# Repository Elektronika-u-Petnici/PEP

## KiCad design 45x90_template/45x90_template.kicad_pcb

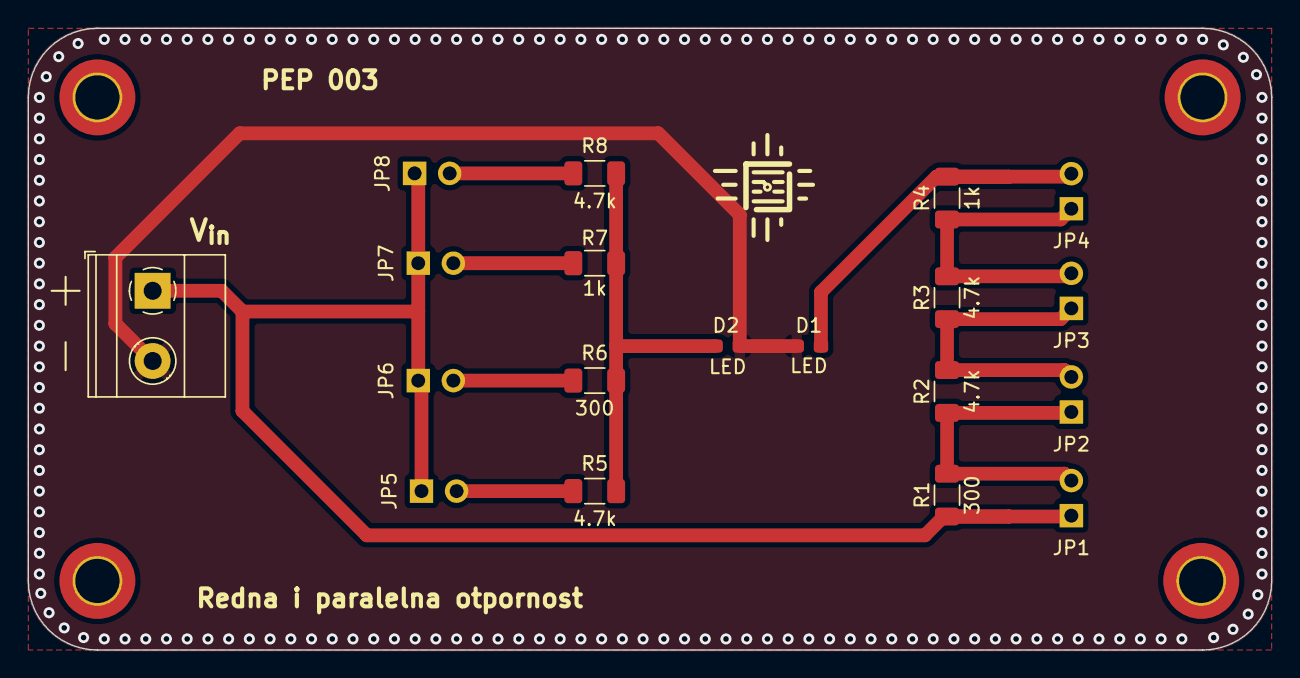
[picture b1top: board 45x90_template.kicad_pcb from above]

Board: 2 copper layers, 90.0 x 45.0 mm, 23 parts (0 on the bottom side), 11 nets.

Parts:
D1, D2: LED; LED_0603_1608Metric_Pad1.05x0.95mm_HandSolder
H1, H2, H3, H4: MountingHole; MountingHole_3.2mm_M3_ISO14580_Pad_TopBottom
J1: Screw_Terminal_01x02; TerminalBlock_Phoenix_MKDS-1,5-2-5.08_1x02_P5.08mm_Horizont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
JP1, JP2, JP3, JP4, JP5, JP6, JP7, JP8: Jumper; PinHeader_1x02_P2.54mm_Vertical
R1, R6: 300; R_smd
R2, R3, R5, R8: 4.7k; R_smd
R4, R7: 1k; R_smd

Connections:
0: D1.1 (K), D2.1 (K), J1.2
9V: J1.1, JP1.1 (A), JP5.1 (A), JP6.1 (A), JP7.1 (A), JP8.1 (A), R1.1
unnamed: D1.2 (A), JP4.2 (B), R4.2
unnamed: D2.2 (A), R5.1, R6.2, R7.2, R8.1
unnamed: JP1.2 (B), JP2.1 (A), R1.2, R2.1
unnamed: JP2.2 (B), JP3.1 (A), R2.2, R3.1
unnamed: JP3.2 (B), JP4.1 (A), R3.2, R4.1
unnamed: JP5.2 (B), R5.2
unnamed: JP6.2 (B), R6.1
unnamed: JP7.2 (B), R7.1
unnamed: JP8.2 (B), R8.2

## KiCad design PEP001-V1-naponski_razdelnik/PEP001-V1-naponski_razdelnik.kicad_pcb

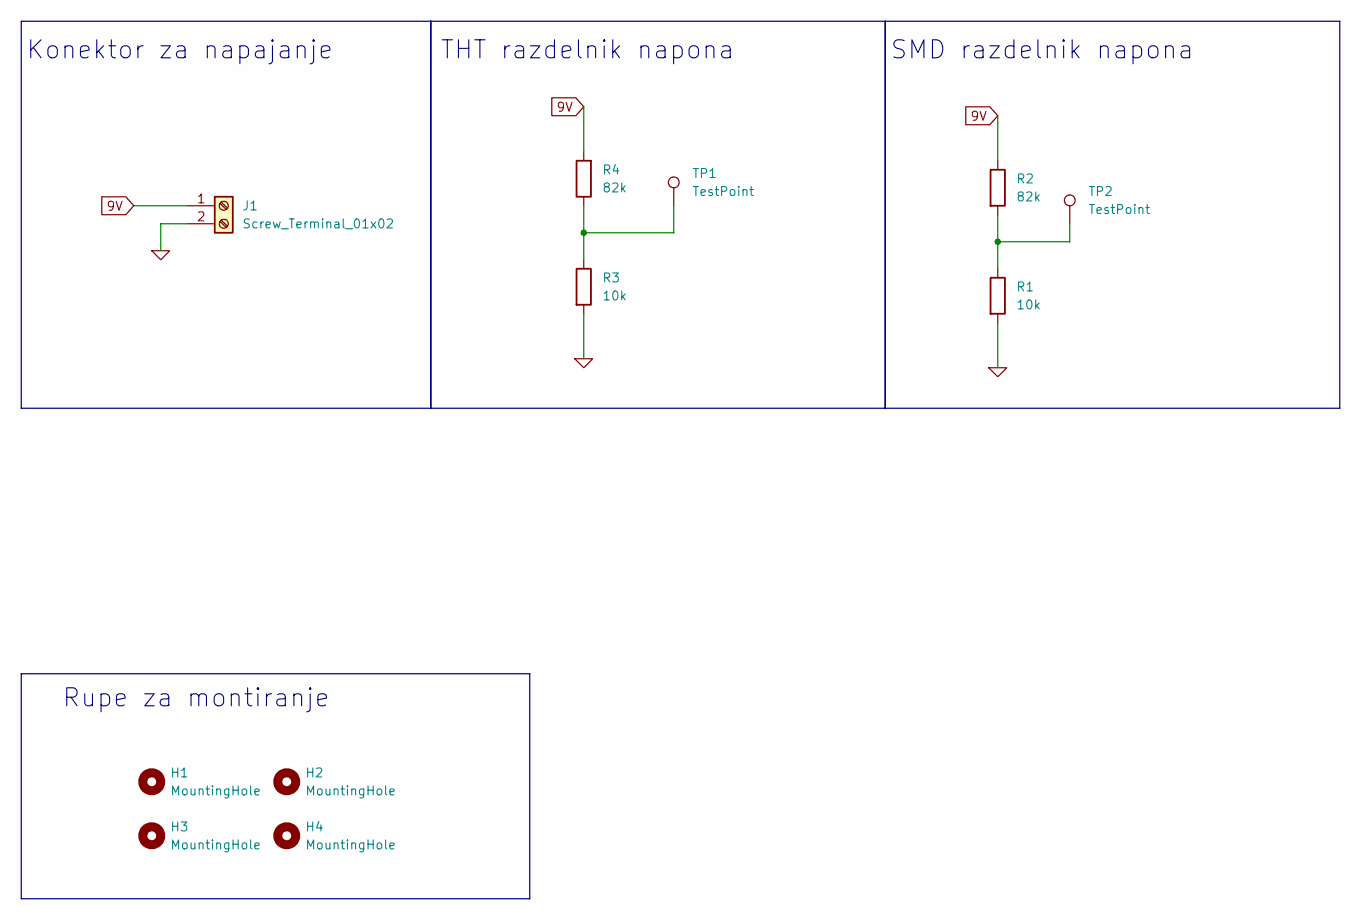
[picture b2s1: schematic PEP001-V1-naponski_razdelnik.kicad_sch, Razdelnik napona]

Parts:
H1, H2, H3, H4: MountingHole; MountingHole_3.2mm_M3_ISO14580_Pad_TopBottom
J1: Screw_Terminal_01x02; TerminalBlock_Phoenix_MKDS-1,5-2-5.08_1x02_P5.08mm_Horizont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; LCSC C3018698
R1: 10k; R_1206_3216Metric_Pad1.30x1.75mm_HandSolder; LCSC C17902
R2: 82k; R_1206_3216Metric_Pad1.30x1.75mm_HandSolder; LCSC C17979
R3: 10k; R_Axial_DIN0207_L6.3mm_D2.5mm_P15.24mm_Horizontal; LCSC C410695
R4: 82k; R_Axial_DIN0207_L6.3mm_D2.5mm_P15.24mm_Horizontal; LCSC C601724
TP1, TP2: TestPoint; TestPoint_Pad_D2.5mm

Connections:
0: J1.2, R1.2, R3.2
9V: J1.1, R2.1, R4.2
unnamed: R1.1, R2.2, TP2.1
unnamed: R3.1, R4.1, TP1.1

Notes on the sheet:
SMD razdelnik napona
Rupe za montiranje
Konektor za napajanje
THT razdelnik napona

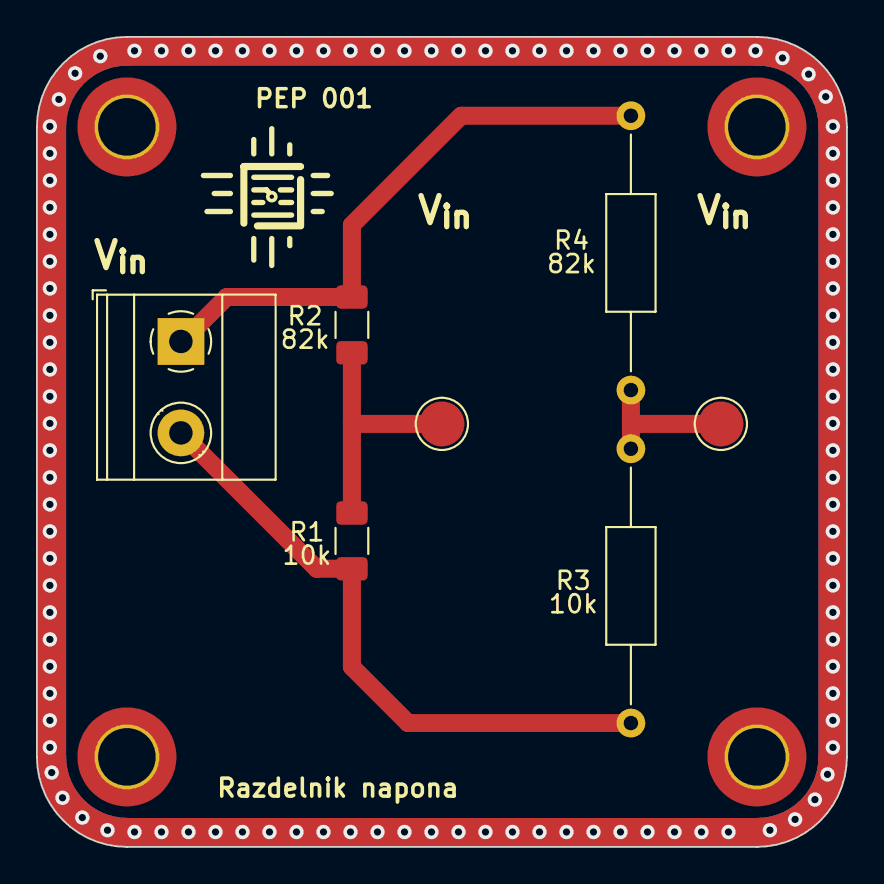
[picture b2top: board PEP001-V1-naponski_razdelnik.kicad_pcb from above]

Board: 2 copper layers, 45.0 x 45.0 mm, 11 parts (0 on the bottom side), 4 nets.

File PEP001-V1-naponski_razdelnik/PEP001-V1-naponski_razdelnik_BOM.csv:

"Comment","Designator","Footprint","LCSC Part Number"
"MountingHole,TestPoint","H1,H2,H3,H4,TP1,TP2","",""
"Screw_Terminal_01x02","J1","THT","C3018698"
"10k","R1","1206","C17902"
"82k","R2","1206","C17979"
"10k","R3","THT","C410695"
"82k","R4","THT","C601724"

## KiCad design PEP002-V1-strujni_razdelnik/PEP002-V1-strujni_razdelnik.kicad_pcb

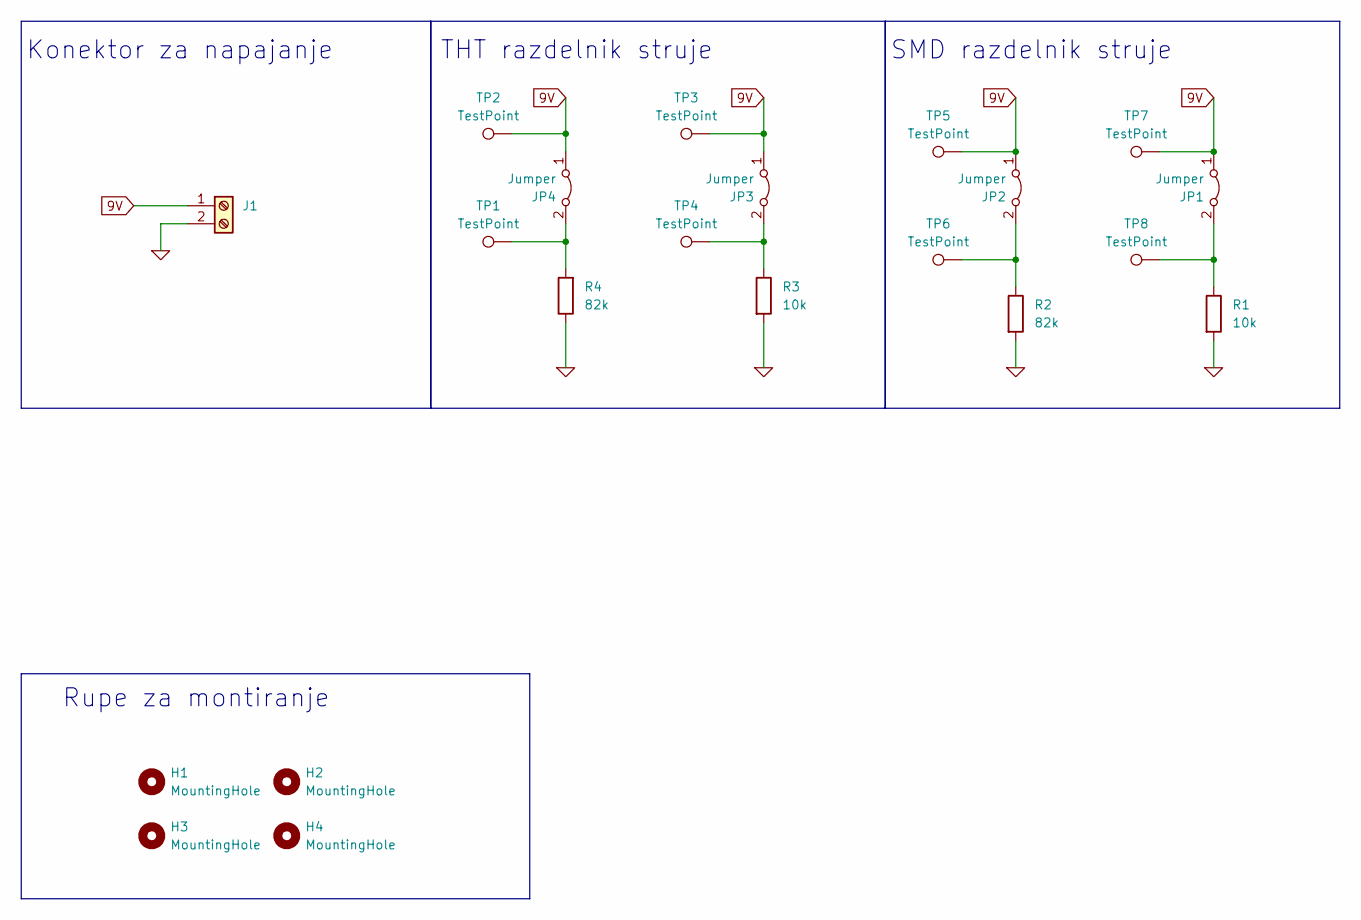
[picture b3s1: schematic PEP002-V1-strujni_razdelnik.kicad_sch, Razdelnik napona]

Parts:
H1, H2, H3, H4: MountingHole; MountingHole_3.2mm_M3_ISO14580_Pad_TopBottom
J1: Screw_Terminal_01x02; TerminalBlock_Phoenix_MKDS-1,5-2-5.08_1x02_P5.08mm_Horizont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; LCSC Part Number C3018698
JP1, JP2, JP3, JP4: Jumper; PinHeader_1x02_P2.54mm_Vertical; LCSC Part Number C492401
R1: 10k; R_1206_3216Metric_Pad1.30x1.75mm_HandSolder; LCSC Part Number C17902
R2: 82k; R_1206_3216Metric_Pad1.30x1.75mm_HandSolder; LCSC Part Number C17979
R3: 10k; R_Axial_DIN0207_L6.3mm_D2.5mm_P15.24mm_Horizontal; LCSC Part Number C410695
R4: 82k; R_Axial_DIN0207_L6.3mm_D2.5mm_P15.24mm_Horizontal; LCSC Part Number C601724
TP1, TP2, TP3, TP4, TP5, TP6, TP7, TP8: TestPoint; TestPoint_Pad_D2.5mm

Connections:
0: J1.2, R1.2, R2.2, R3.2, R4.1
9V: J1.1, JP1.1 (A), JP2.1 (A), JP3.1 (A), JP4.1 (A), TP2.1, TP3.1, TP5.1, TP7.1
unnamed: JP1.2 (B), R1.1, TP8.1
unnamed: JP2.2 (B), R2.1, TP6.1
unnamed: JP3.2 (B), R3.1, TP4.1
unnamed: JP4.2 (B), R4.2, TP1.1

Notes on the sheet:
SMD razdelnik struje
Rupe za montiranje
Konektor za napajanje
THT razdelnik struje

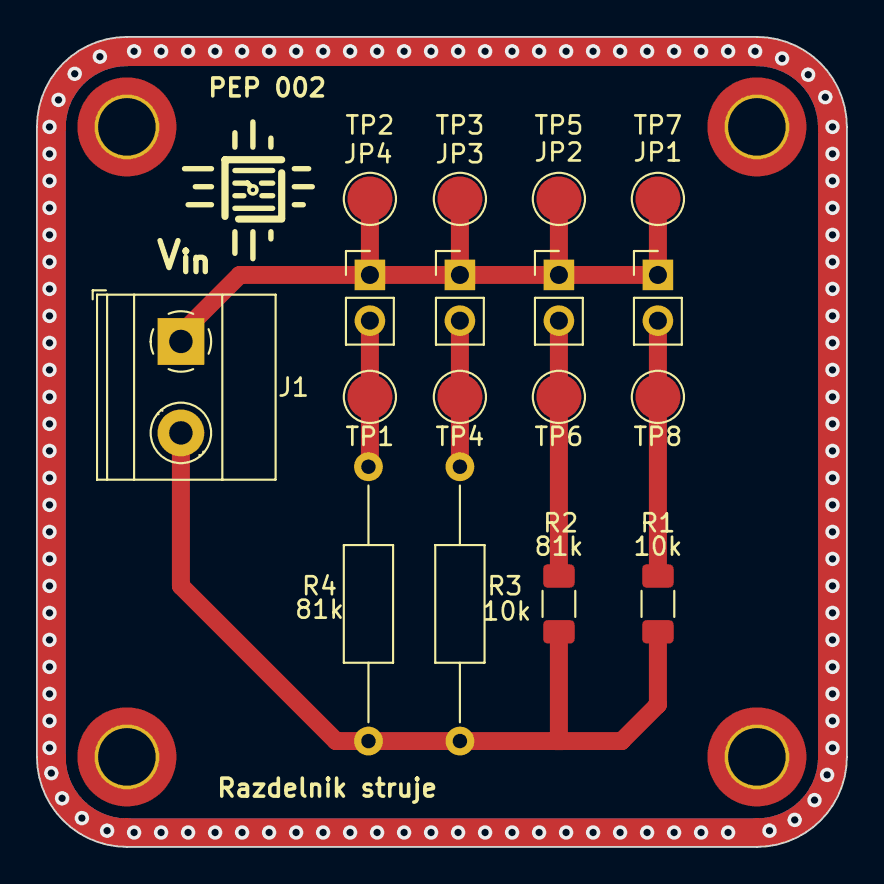
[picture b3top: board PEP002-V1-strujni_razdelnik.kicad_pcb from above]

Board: 2 copper layers, 45.0 x 45.0 mm, 21 parts (0 on the bottom side), 6 nets.

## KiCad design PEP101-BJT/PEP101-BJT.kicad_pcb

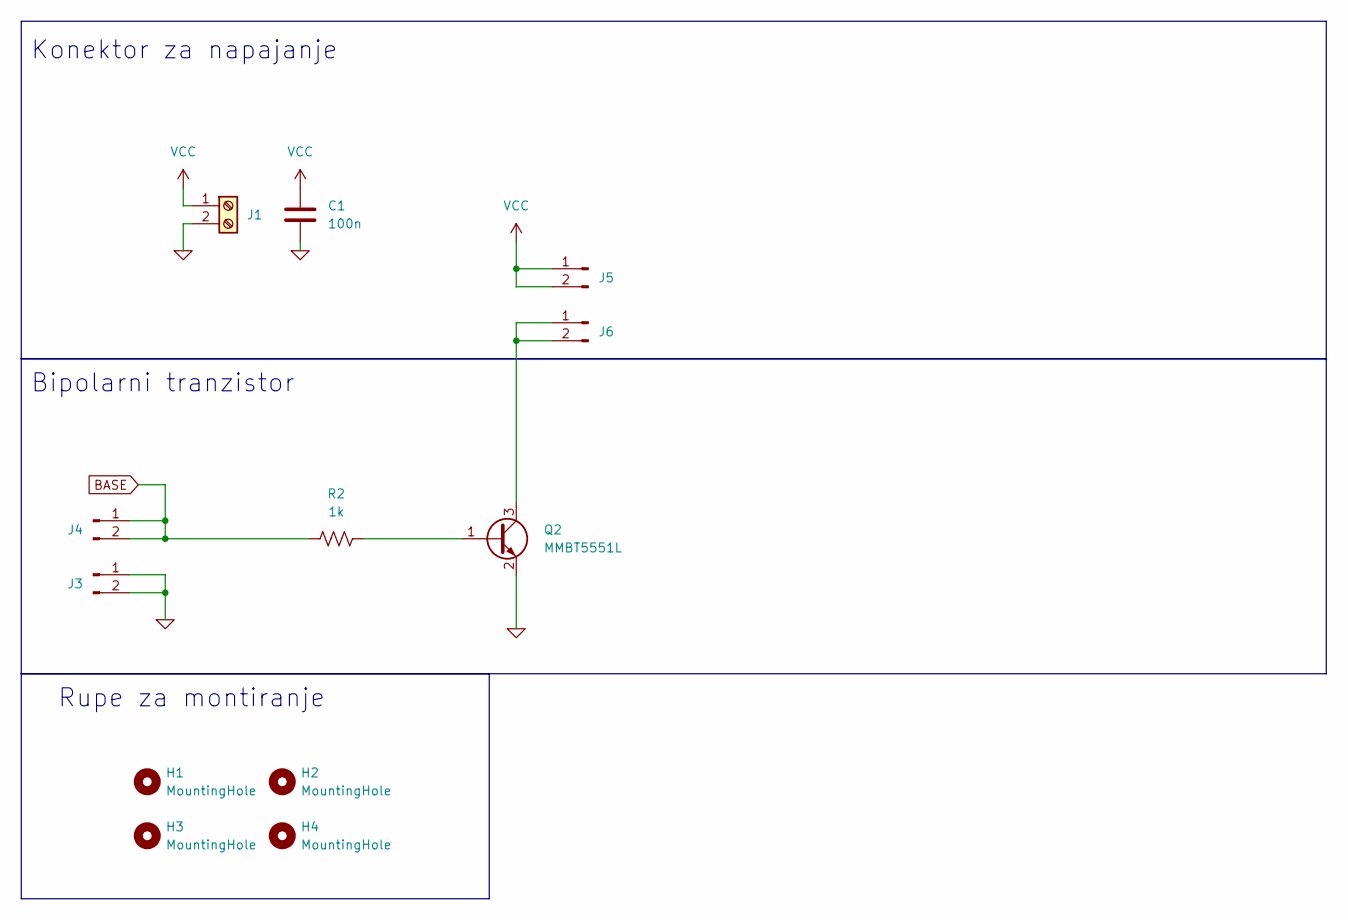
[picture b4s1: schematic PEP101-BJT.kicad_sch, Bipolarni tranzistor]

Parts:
C1: 100n; C_1206_3216Metric_Pad1.33x1.80mm_HandSolder; LCSC C24497
H1, H2, H3, H4: MountingHole; MountingHole_3.2mm_M3_ISO14580_Pad_TopBottom
J1: Screw_Terminal_01x02; TerminalBlock_Phoenix_MKDS-1,5-2-5.08_1x02_P5.08mm_Horizont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
J3, J4, J5, J6: Conn_01x02_Pin; PinHeader_2x01_P2.54mm_Vertical
Q2: MMBT5551L; SOT-23; LCSC C2145
R2: 1k; R_1206_3216Metric_Pad1.30x1.75mm_HandSolder; LCSC C4410

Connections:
0: C1.2, J1.2, J3.1, J3.2, Q2.2 (E)
BASE: J4.1, J4.2, R2.1
unnamed: J6.1, J6.2, Q2.3 (C)
unnamed: Q2.1 (B), R2.2
VCC: C1.1, J1.1, J5.1, J5.2

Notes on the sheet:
Bipolarni tranzistor
Rupe za montiranje
Konektor za napajanje

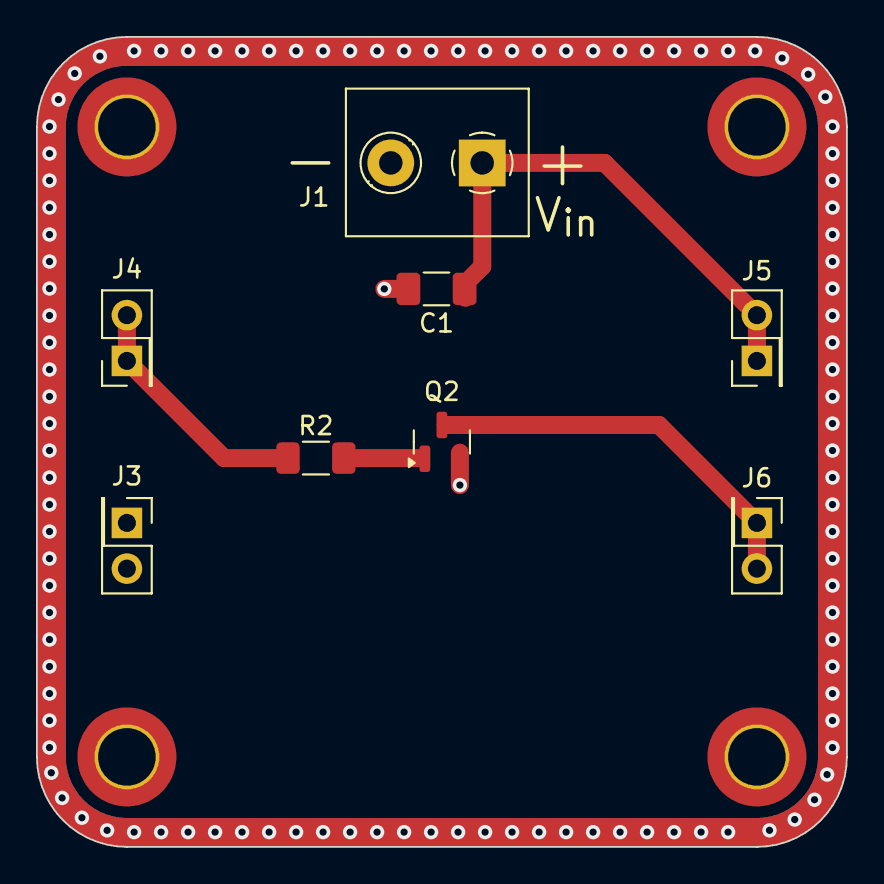
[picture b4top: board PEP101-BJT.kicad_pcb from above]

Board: 2 copper layers, 45.0 x 45.0 mm, 12 parts (0 on the bottom side), 5 nets.

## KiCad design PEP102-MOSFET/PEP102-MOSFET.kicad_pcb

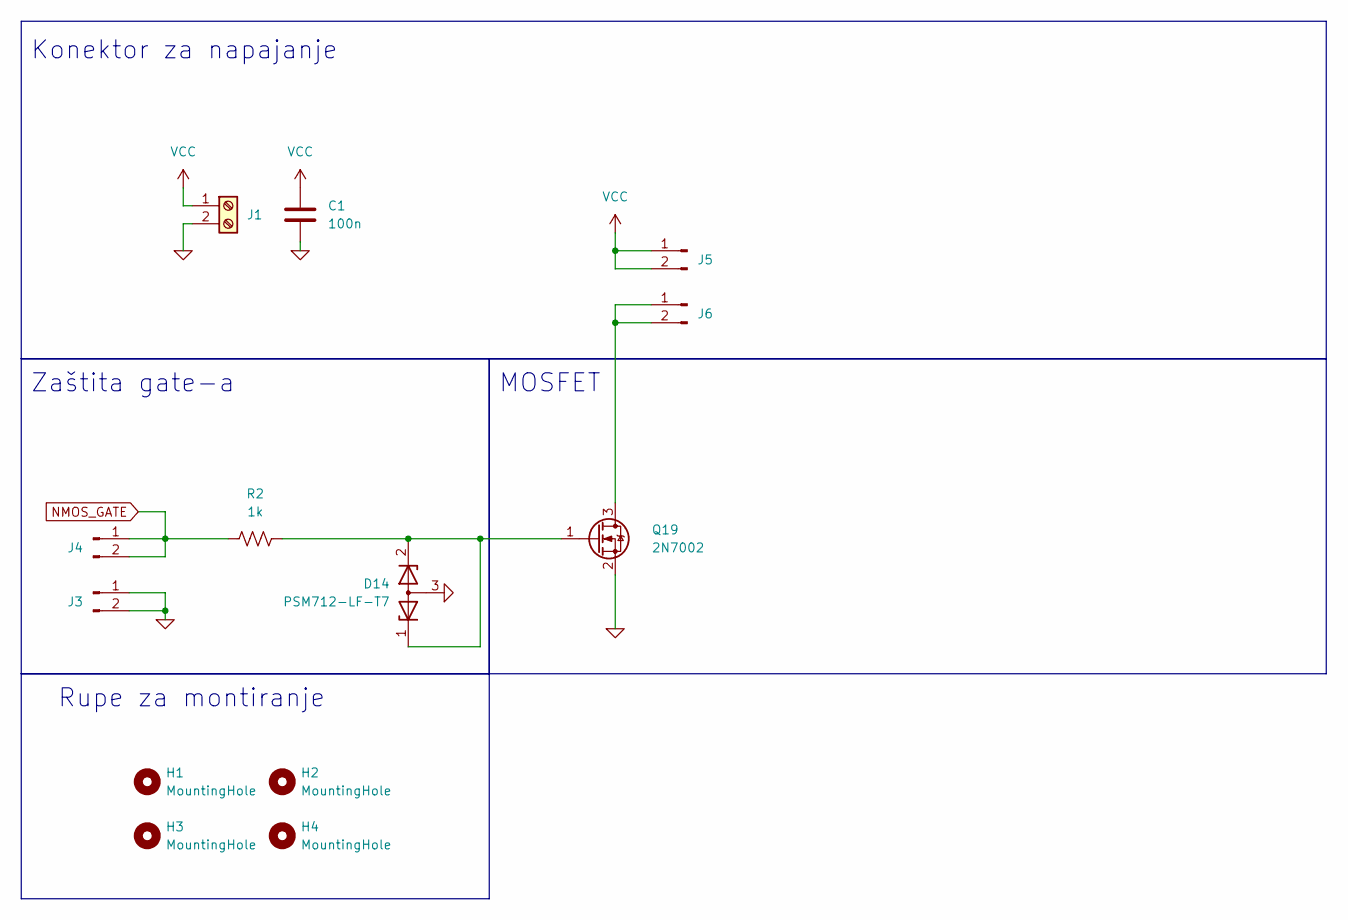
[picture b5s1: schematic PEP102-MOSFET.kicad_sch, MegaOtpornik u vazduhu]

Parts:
C1: 100n; C_1206_3216Metric_Pad1.33x1.80mm_HandSolder; LCSC C24497
D14: PSM712-LF-T7; SOT-23; LCSC C32677
H1, H2, H3, H4: MountingHole; MountingHole_3.2mm_M3_ISO14580_Pad_TopBottom
J1: Screw_Terminal_01x02; TerminalBlock_Phoenix_MKDS-1,5-2-5.08_1x02_P5.08mm_Horizont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
J3, J4, J5, J6: Conn_01x02_Pin; PinHeader_2x01_P2.54mm_Vertical
Q19: 2N7002; SOT-23; LCSC C8545
R2: 1k; R_1206_3216Metric_Pad1.30x1.75mm_HandSolder; LCSC C4410

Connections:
0: C1.2, D14.3 (A), J1.2, J3.1, J3.2, Q19.2 (S); also elsewhere on the board
NMOS_GATE: J4.1, J4.2, R2.1
unnamed: J6.1, J6.2, Q19.3 (D)
unnamed: D14.1 (K), D14.2 (K), Q19.1 (G), R2.2
VCC: C1.1, J1.1, J5.1, J5.2; also elsewhere on the board

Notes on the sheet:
Zaštita gate-a
Rupe za montiranje
Konektor za napajanje
MOSFET

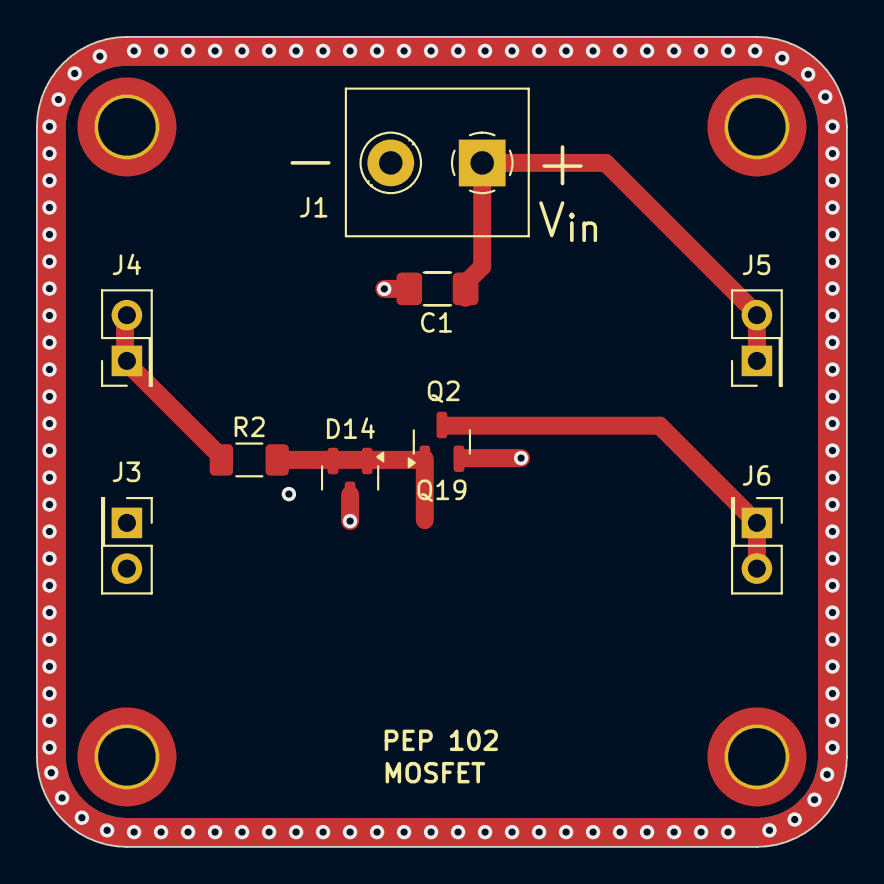
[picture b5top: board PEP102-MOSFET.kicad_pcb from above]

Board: 2 copper layers, 45.0 x 45.0 mm, 14 parts (0 on the bottom side), 5 nets.

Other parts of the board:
C1#2: 100n; C_1206_3216Metric_Pad1.33x1.80mm_HandSolder

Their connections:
0: C1#2.2; also elsewhere on the board
VCC: C1#2.1; also elsewhere on the board

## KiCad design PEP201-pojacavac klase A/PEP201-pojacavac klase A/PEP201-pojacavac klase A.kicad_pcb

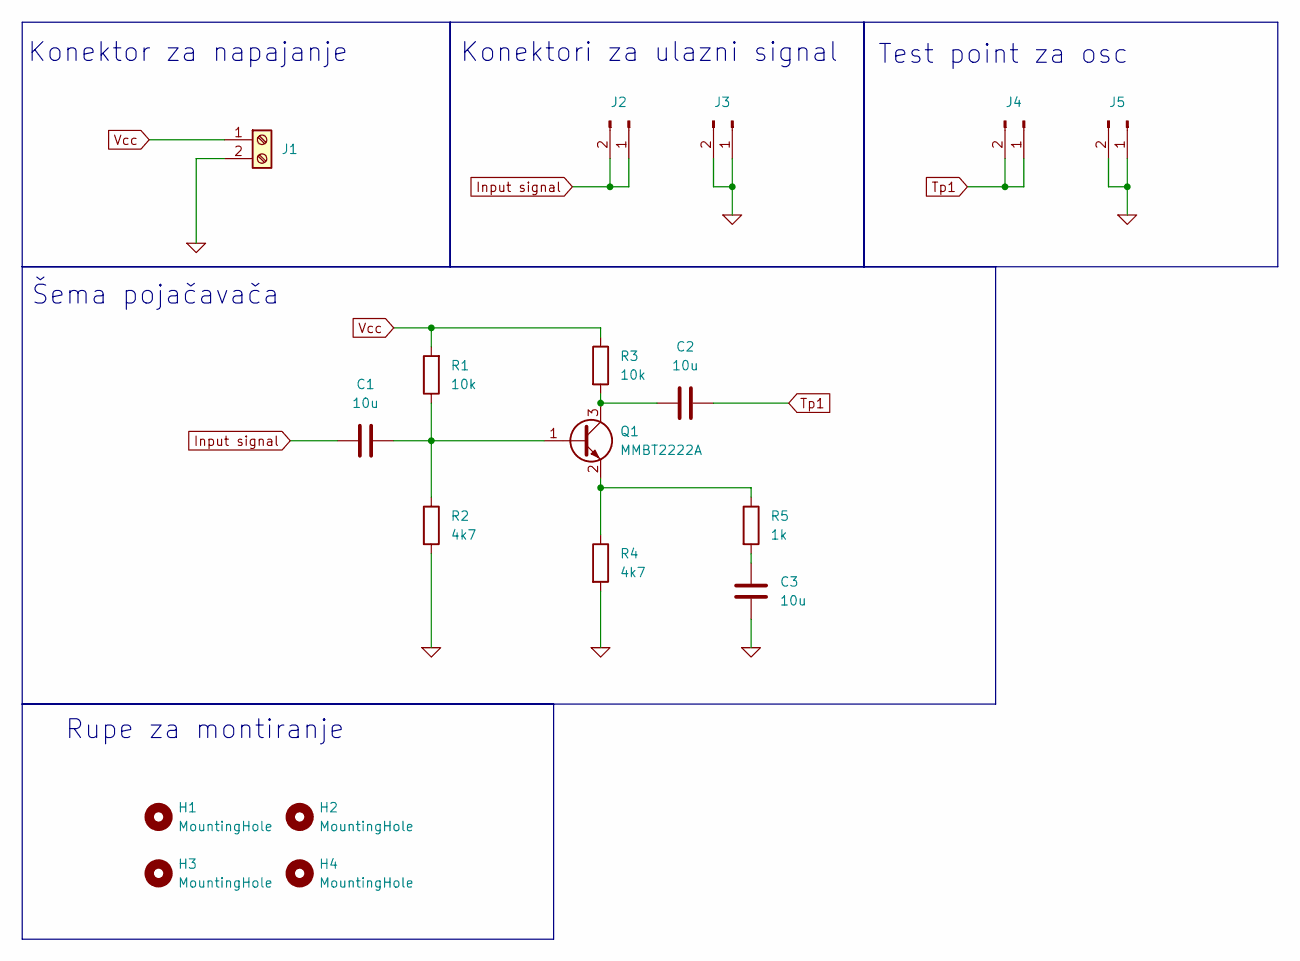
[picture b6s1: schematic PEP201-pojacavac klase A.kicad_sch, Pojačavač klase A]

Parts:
C1, C2, C3: 10u; C_1206_3216Metric_Pad1.33x1.80mm_HandSolder; LCSC C13585
H1, H2, H3, H4: MountingHole; MountingHole_3.2mm_M3_ISO14580_Pad_TopBottom
J1: Screw_Terminal_01x02; TerminalBlock_Phoenix_MKDS-1,5-2-5.08_1x02_P5.08mm_Horizont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
J2, J3, J4, J5: Conn_01x02_Pin; PinHeader_1x02_P2.54mm_Vertical
Q1: MMBT2222A; SOT-23; LCSC C8512
R1, R3: 10k; R_1206_3216Metric_Pad1.30x1.75mm_HandSolder; LCSC C17902
R2, R4: 4k7; R_1206_3216Metric_Pad1.30x1.75mm_HandSolder; LCSC C17936
R5: 1k; R_1206_3216Metric_Pad1.30x1.75mm_HandSolder; LCSC C4410

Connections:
0: C3.2, J1.2, J3.1, J3.2, J5.1, J5.2, R2.2, R4.2
Input signal: C1.1, J2.1, J2.2
unnamed: C3.1, R5.2
unnamed: C1.2, Q1.1 (B), R1.1, R2.1
unnamed: C2.1, Q1.3 (C), R3.2
unnamed: Q1.2 (E), R4.1, R5.1
Tp1: C2.2, J4.1, J4.2
Vcc: J1.1, R1.2, R3.1

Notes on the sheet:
Rupe za montiranje
Test point za osc
Konektor za napajanje
Šema pojačavača
Konektori za ulazni signal

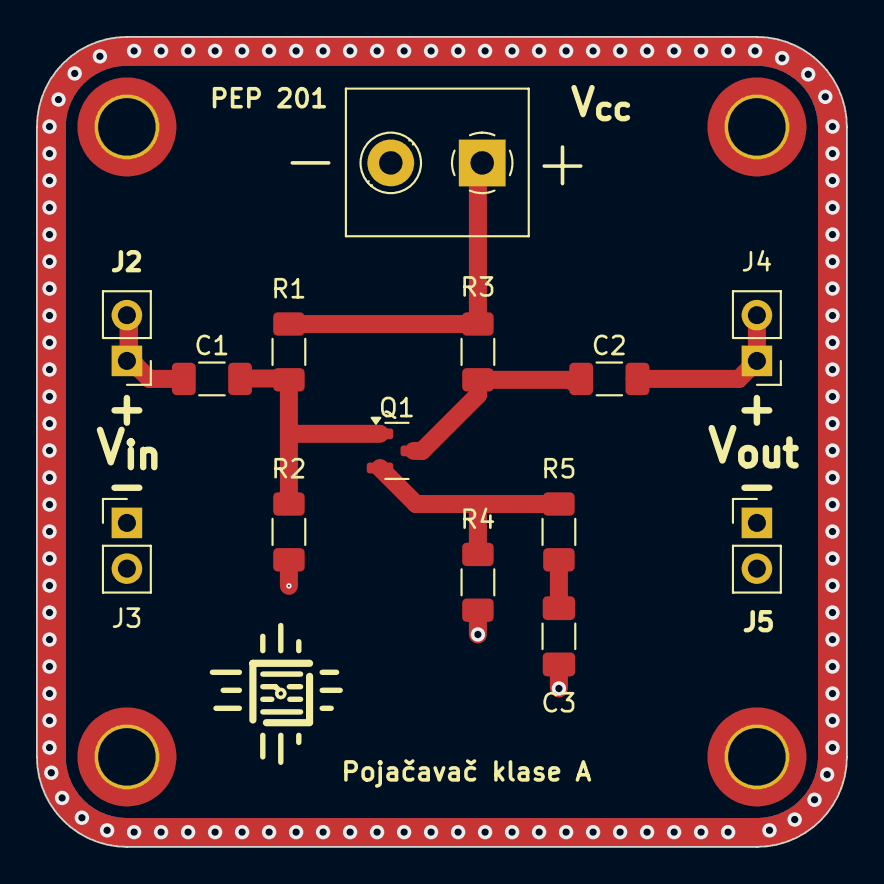
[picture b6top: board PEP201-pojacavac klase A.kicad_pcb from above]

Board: 2 copper layers, 45.0 x 45.0 mm, 18 parts (0 on the bottom side), 8 nets.
